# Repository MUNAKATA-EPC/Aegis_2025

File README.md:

🏆 Competition Results

<2024 Season>
Kitakyushu Node Tournament → 🥇 Champion (A Court)

Kyushu Block Tournament → 🥇 Champion, 🏅 Best Presentation Award

Japan Open 2024 Soccer Lightweight League → 31st place

<2025 Season>
Fukuoka Node Tournament → 🥇 Champion

Kyushu Block Tournament → 🥇 Champion

Japan Open 2025 Soccer Lightweight League → 🥇 Champion, 🏅 Best Presentation Award

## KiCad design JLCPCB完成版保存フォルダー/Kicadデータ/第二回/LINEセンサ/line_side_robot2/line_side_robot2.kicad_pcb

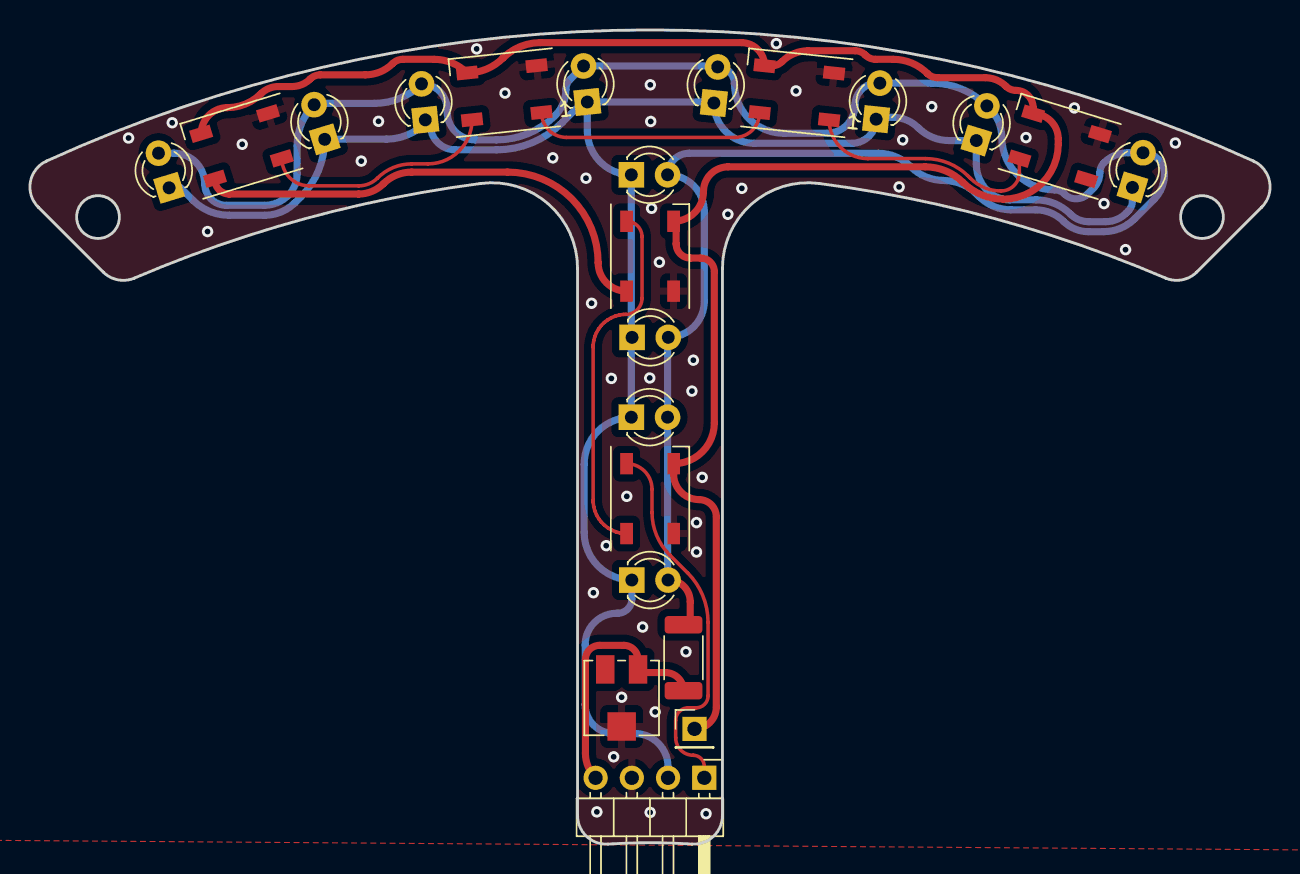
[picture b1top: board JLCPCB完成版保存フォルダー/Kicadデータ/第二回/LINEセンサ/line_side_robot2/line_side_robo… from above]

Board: 2 copper layers, 87.0 x 57.1 mm, 22 parts (0 on the bottom side), 11 nets.

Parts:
D1, D2, D3, D4, D5, D6: NeoPixel_THT; LED_WS2812B_PLCC4_5.0x5.0mm_P3.2mm
J1: Conn_01x04_Pin; PinHeader_1x04_P2.54mm_Horizontal
J2: Conn_01x01_Pin; PinHeader_1x01_P2.54mm_Vertical
Q1, Q2, Q3, Q4, Q5, Q6, Q7, Q8, Q9, Q10, Q11, Q12: Q_Photo_NPN; LED_D3.0mm_Clear
R1: 1K; R_2010_5025Metric
RV1: R_Potentiometer_Trim_US; Potentiometer_Vishay_TS53YJ_Vertical

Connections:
+3.3V: J1.2, Q1.1 (C), Q2.1 (C), Q3.1 (C), Q4.1 (C), Q5.1 (C), Q6.1 (C), Q7.1 (C), Q8.1 (C), Q9.1 (C), Q10.1 (C), Q11.1 (C), Q12.1 (C)
+5V: D1.3 (VDD), D2.3 (VDD), D3.3 (VDD), D4.3 (VDD), D5.3 (VDD), D6.3 (VDD), J2.1
/PWM: D1.4 (DIN), J1.1
/S: J1.4, R1.1, RV1.3
GND: D1.2 (GND), D2.2 (GND), D3.2 (GND), D4.2 (GND), D5.2 (GND), D6.2 (GND), J1.3, RV1.2
unnamed: D1.1 (DOUT), D2.4 (DIN)
unnamed: D2.1 (DOUT), D3.4 (DIN)
unnamed: D3.1 (DOUT), D6.4 (DIN)
unnamed: D4.4 (DIN), D6.1 (DOUT)
unnamed: D4.1 (DOUT), D5.4 (DIN)
unnamed: Q1.2 (E), Q2.2 (E), Q3.2 (E), Q4.2 (E), Q5.2 (E), Q6.2 (E), Q7.2 (E), Q8.2 (E), Q9.2 (E), Q10.2 (E), Q11.2 (E), Q12.2 (E), R1.2

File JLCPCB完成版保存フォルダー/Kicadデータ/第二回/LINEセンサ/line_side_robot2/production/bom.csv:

Designator,Footprint,Quantity,Value,LCSC Part #
"D1, D2, D3, D4, D5, D6",LED_WS2812B_PLCC4_5.0x5.0mm_P3.2mm,6,NeoPixel_THT,
J1,PinHeader_1x04_P2.54mm_Horizontal,1,Conn_01x04_Pin,
J2,PinHeader_1x01_P2.54mm_Vertical,1,Conn_01x01_Pin,
"Q1, Q10, Q11, Q12, Q2, Q3, Q4, Q5, Q6, Q7, Q8, Q9",LED_D3.0mm_Clear,12,Q_Photo_NPN,
R1,2010,1,1K,
RV1,Potentiometer_Vishay_TS53YJ_Vertical,1,R_Potentiometer_Trim_US,

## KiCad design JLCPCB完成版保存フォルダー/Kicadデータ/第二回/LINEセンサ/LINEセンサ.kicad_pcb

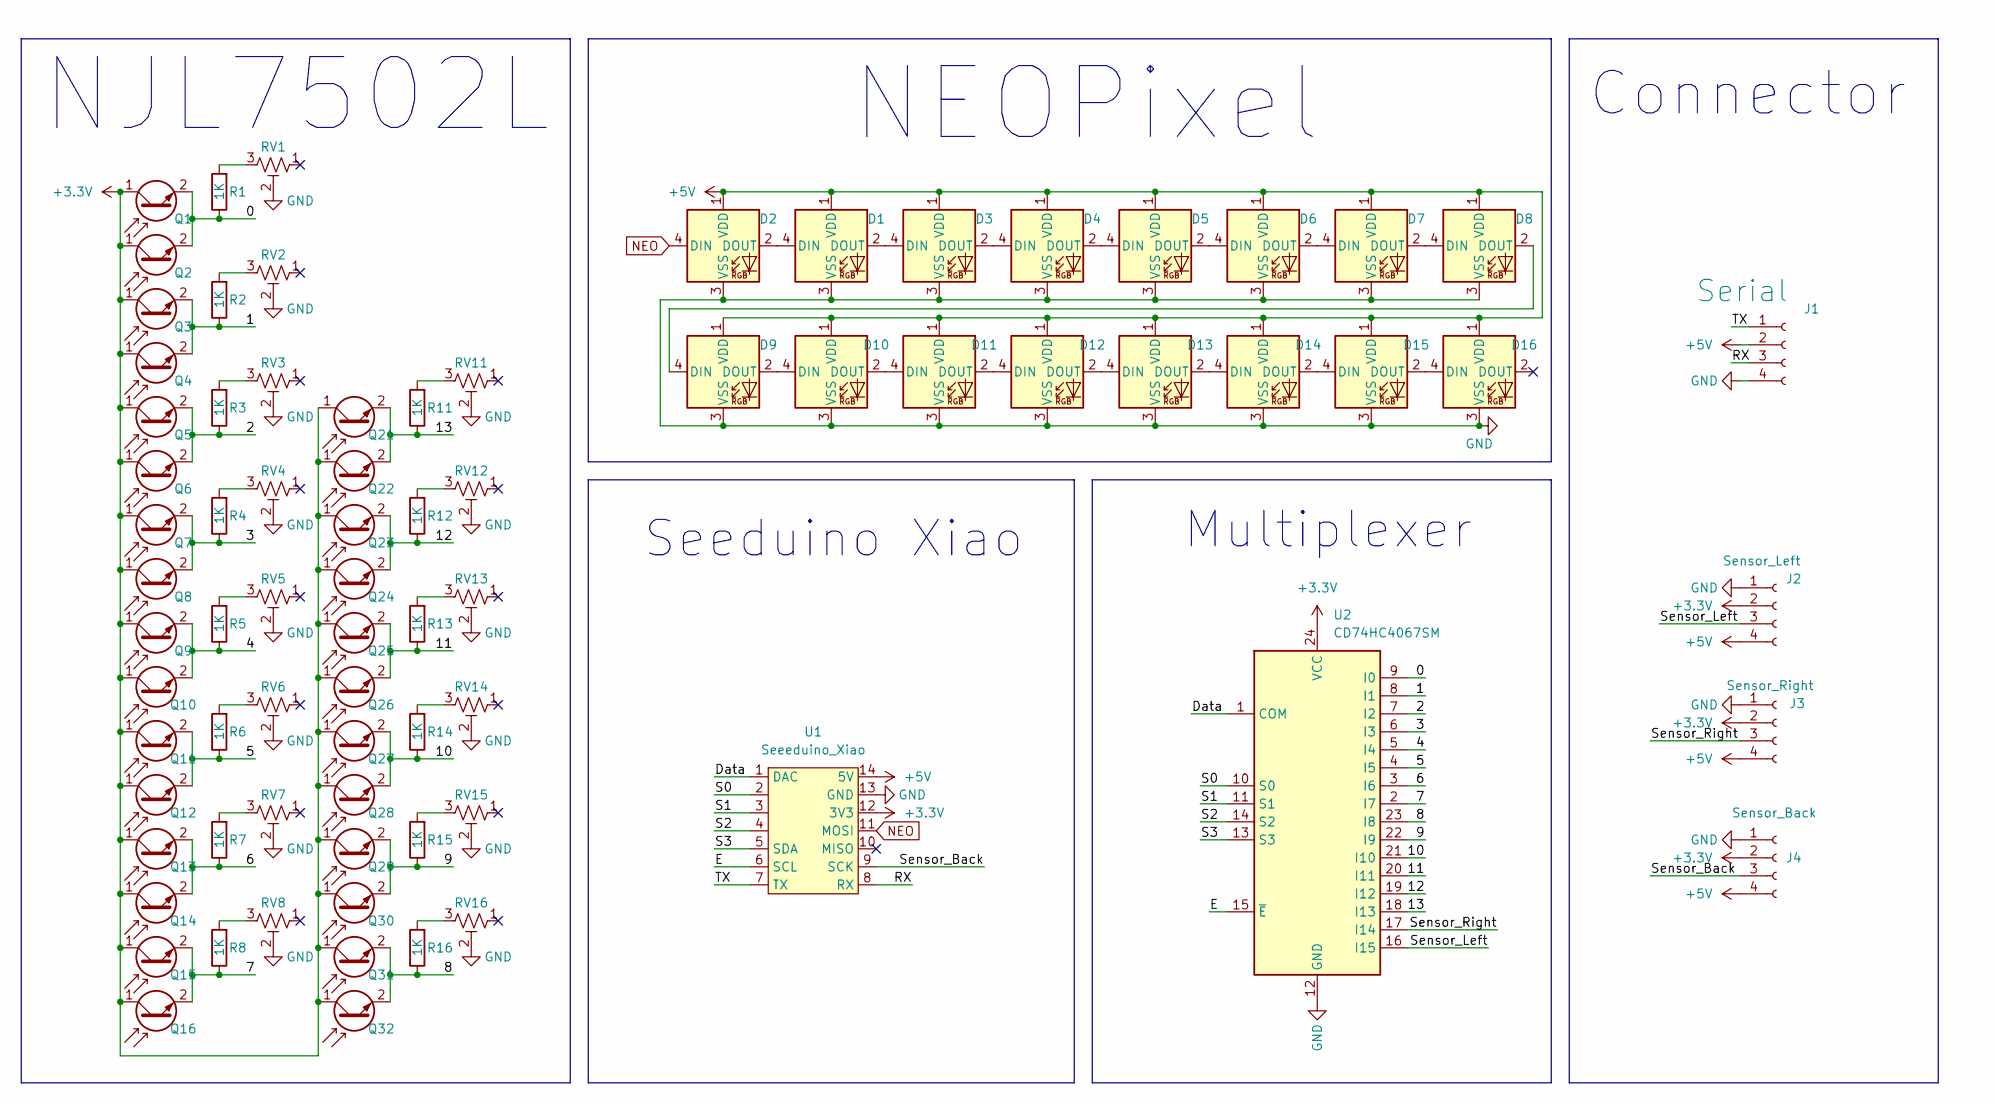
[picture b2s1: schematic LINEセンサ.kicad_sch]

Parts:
D1: WS2812B; JST_XH_B4B-XH-A_1x04_P2.50mm_Vertical
D2, D3, D4, D5, D6, D7, D8, D9, D10, D11, D12, D13, D14, D15, D16: WS2812B; LED_WS2812B-2020_PLCC4_2.0x2.0mm
J1: Serial; JST_XH_B4B-XH-A_1x04_P2.50mm_Vertical
J2: Sensor_Left; JST_XH_B4B-XH-A_1x04_P2.50mm_Vertical
J3: Sensor_Right; JST_XH_B4B-XH-A_1x04_P2.50mm_Vertical
J4: Sensor_Back; JST_XH_B4B-XH-A_1x04_P2.50mm_Vertical
Q1, Q2, Q3, Q4, Q5, Q6, Q7, Q8, Q9, Q10, Q11, Q12, Q13, Q14, Q15, Q16, Q21, Q22, Q23, Q24, Q25, Q26, Q27, Q28, Q29, Q30, Q31, Q32: Q_Photo_NPN; LED_D3.0mm_Clear
R1, R2, R3, R4, R5, R6, R7, R8, R11, R12, R13, R14, R15, R16: 1K; R_2010_5025Metric
RV1, RV2, RV3, RV4, RV5, RV6, RV7, RV8, RV11, RV12, RV13, RV14, RV15, RV16: R_Potentiometer_Trim_US; Potentiometer_Vishay_TS53YJ_Vertical
U1: Seeeduino_Xiao; seeeduinoXIAO
U2: CD74HC4067SM; SSOP-24_5.3x8.2mm_P0.65mm

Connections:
+3.3V: J2.2, J3.2, J4.2, Q1.1 (C), Q2.1 (C), Q3.1 (C), Q4.1 (C), Q5.1 (C), Q6.1 (C), Q7.1 (C), Q8.1 (C), Q9.1 (C), Q10.1 (C), Q11.1 (C), Q12.1 (C), Q13.1 (C), Q14.1 (C), Q15.1 (C), Q16.1 (C), Q21.1 (C), Q22.1 (C), Q23.1 (C), Q24.1 (C), Q25.1 (C), Q26.1 (C), Q27.1 (C), Q28.1 (C), Q29.1 (C), Q30.1 (C), Q31.1 (C), Q32.1 (C), U1.12 (3V3), U2.24 (VCC)
+5V: D1.1 (VDD), D2.1 (VDD), D3.1 (VDD), D4.1 (VDD), D5.1 (VDD), D6.1 (VDD), D7.1 (VDD), D8.1 (VDD), D9.1 (VDD), D10.1 (VDD), D11.1 (VDD), D12.1 (VDD), D13.1 (VDD), D14.1 (VDD), D15.1 (VDD), D16.1 (VDD), J1.2, J2.4, J3.4, J4.4, U1.14 (5V)
/0: Q1.2 (E), Q2.2 (E), R1.1, U2.9 (I0)
/1: Q3.2 (E), Q4.2 (E), R2.1, U2.8 (I1)
/2: Q5.2 (E), Q6.2 (E), R3.1, U2.7 (I2)
/3: Q7.2 (E), Q8.2 (E), R4.1, U2.6 (I3)
/4: Q9.2 (E), Q10.2 (E), R5.1, U2.5 (I4)
/5: Q11.2 (E), Q12.2 (E), R6.1, U2.4 (I5)
/6: Q13.2 (E), Q14.2 (E), R7.1, U2.3 (I6)
/7: Q15.2 (E), Q16.2 (E), R8.1, U2.2 (I7)
/8: Q31.2 (E), Q32.2 (E), R16.1, U2.23 (I8)
/9: Q29.2 (E), Q30.2 (E), R15.1, U2.22 (I9)
/10: Q27.2 (E), Q28.2 (E), R14.1, U2.21 (I10)
/11: Q25.2 (E), Q26.2 (E), R13.1, U2.20 (I11)
/12: Q23.2 (E), Q24.2 (E), R12.1, U2.19 (I12)
/13: Q21.2 (E), Q22.2 (E), R11.1, U2.18 (I13)
/Data: U1.1 (DAC), U2.1 (COM)
/E: U1.6 (SCL), U2.15 (~E)
/RX: J1.3, U1.8 (RX)
/S0: U1.2, U2.10 (S0)
/S1: U1.3, U2.11 (S1)
/S2: U1.4, U2.14 (S2)
/S3: U1.5 (SDA), U2.13 (S3)
/Sensor_Back: J4.3, U1.9 (SCK)
/Sensor_Left: J2.3, U2.16 (I15)
/Sensor_Right: J3.3, U2.17 (I14)
/TX: J1.1, U1.7 (TX)
GND: D1.3 (VSS), D2.3 (VSS), D3.3 (VSS), D4.3 (VSS), D5.3 (VSS), D6.3 (VSS), D7.3 (VSS), D8.3 (VSS), D9.3 (VSS), D10.3 (VSS), D11.3 (VSS), D12.3 (VSS), D13.3 (VSS), D14.3 (VSS), D15.3 (VSS), D16.3 (VSS), J1.4, J2.1, J3.1, J4.1, RV1.2, RV2.2, RV3.2, RV4.2, RV5.2, RV6.2, RV7.2, RV8.2, RV11.2, RV12.2, RV13.2, RV14.2, RV15.2, RV16.2, U1.13 (GND), U2.12 (GND)
NEO: D2.4 (DIN), U1.11 (MOSI)
unnamed: D1.4 (DIN), D2.2 (DOUT)
unnamed: D1.2 (DOUT), D3.4 (DIN)
unnamed: D3.2 (DOUT), D4.4 (DIN)
unnamed: D4.2 (DOUT), D5.4 (DIN)
unnamed: D5.2 (DOUT), D6.4 (DIN)
unnamed: D6.2 (DOUT), D7.4 (DIN)
unnamed: D7.2 (DOUT), D8.4 (DIN)
unnamed: D8.2 (DOUT), D9.4 (DIN)
unnamed: D9.2 (DOUT), D10.4 (DIN)
unnamed: D10.2 (DOUT), D11.4 (DIN)
unnamed: D11.2 (DOUT), D12.4 (DIN)
unnamed: D12.2 (DOUT), D13.4 (DIN)
unnamed: D13.2 (DOUT), D14.4 (DIN)
unnamed: D14.2 (DOUT), D15.4 (DIN)
unnamed: D15.2 (DOUT), D16.4 (DIN)
unnamed: R1.2, RV1.3
unnamed: R2.2, RV2.3
unnamed: R3.2, RV3.3
unnamed: R4.2, RV4.3
unnamed: R5.2, RV5.3
unnamed: R6.2, RV6.3
unnamed: R7.2, RV7.3
unnamed: R8.2, RV8.3
unnamed: R11.2, RV11.3
unnamed: R12.2, RV12.3
unnamed: R13.2, RV13.3
unnamed: R14.2, RV14.3
unnamed: R15.2, RV15.3
unnamed: R16.2, RV16.3

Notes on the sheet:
NJL7502L
Seeduino Xiao
NEOPixel
Multiplexer
Connector

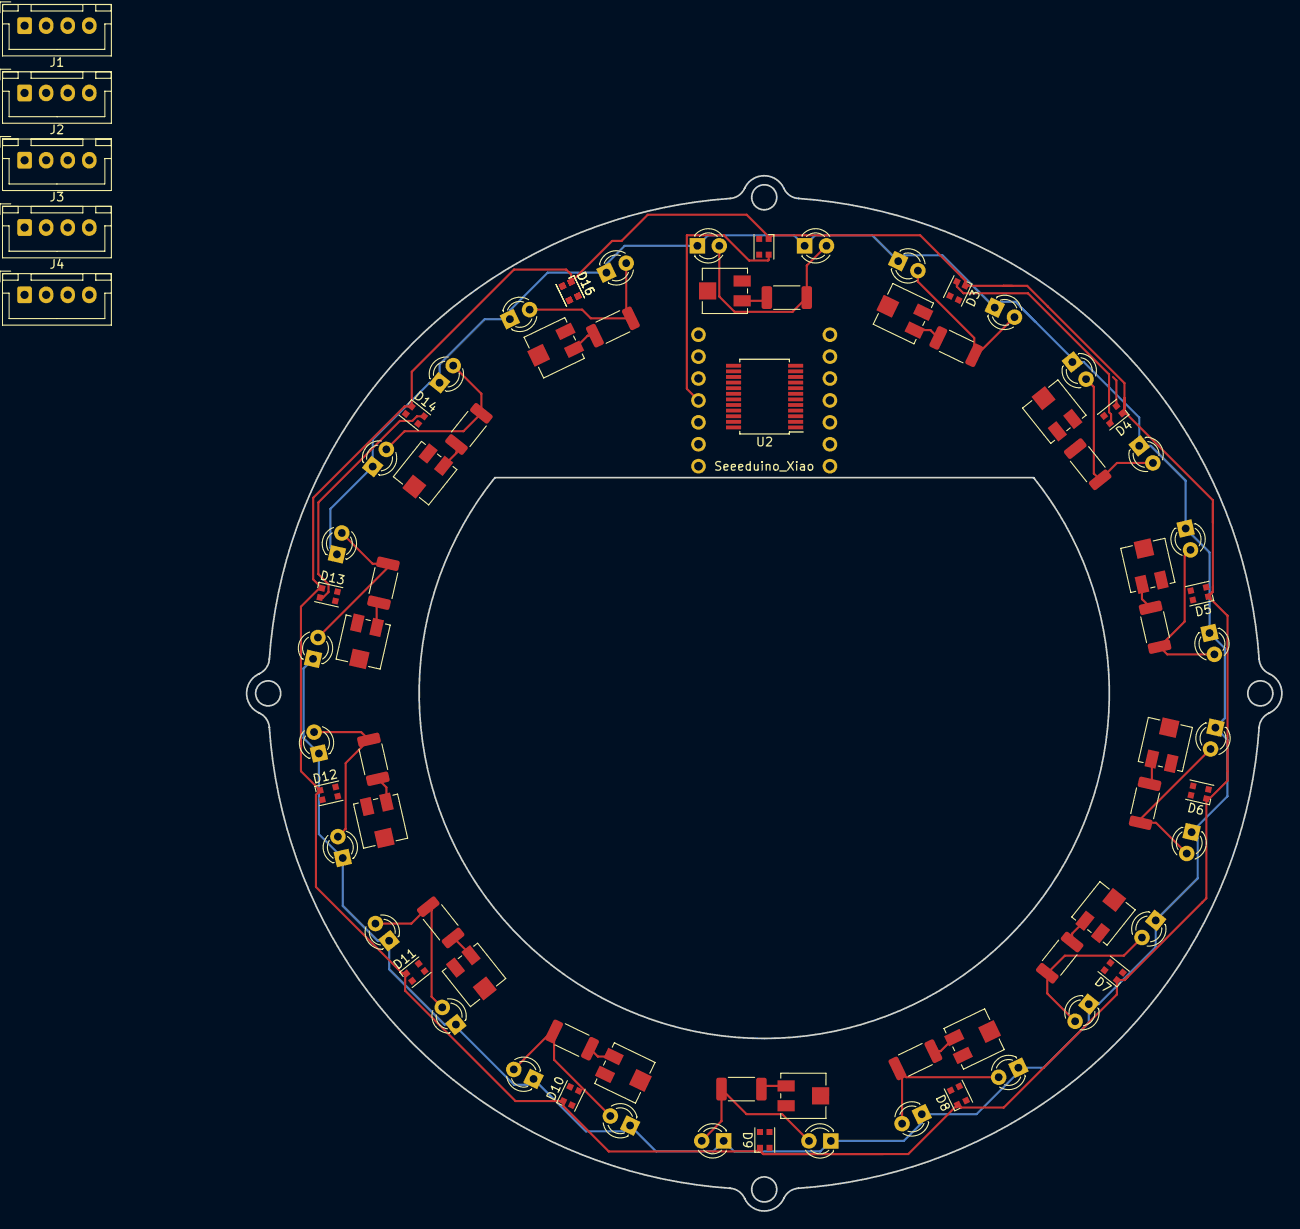
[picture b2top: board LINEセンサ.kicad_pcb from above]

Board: 2 copper layers, 120.0 x 120.0 mm, 78 parts (0 on the bottom side), 58 nets.

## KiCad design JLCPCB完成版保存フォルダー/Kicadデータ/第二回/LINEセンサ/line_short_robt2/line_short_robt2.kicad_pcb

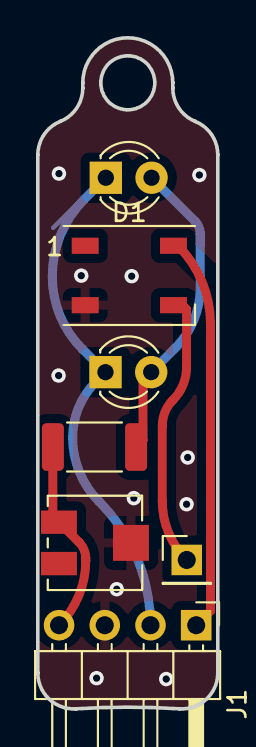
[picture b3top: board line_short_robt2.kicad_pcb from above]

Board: 2 copper layers, 10.0 x 37.3 mm, 7 parts (0 on the bottom side), 6 nets.

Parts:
D1: NeoPixel_THT; LED_WS2812B_PLCC4_5.0x5.0mm_P3.2mm
J1: Conn_01x04_Pin; PinHeader_1x04_P2.54mm_Horizontal
J2: Conn_01x01_Pin; PinHeader_1x01_P2.54mm_Vertical
Q1, Q2: Q_Photo_NPN; LED_D3.0mm_Clear
R1: 1K; R_2010_5025Metric
RV1: R_Potentiometer_Trim_US; Potentiometer_Vishay_TS53YJ_Vertical

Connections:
+3.3V: J1.2, Q1.1 (C), Q2.1 (C)
+5V: D1.3 (VDD), J2.1
/PWM: D1.4 (DIN), J1.1
/S: J1.4, R1.1, RV1.3
GND: D1.2 (GND), J1.3, RV1.2
unnamed: Q1.2 (E), Q2.2 (E), R1.2

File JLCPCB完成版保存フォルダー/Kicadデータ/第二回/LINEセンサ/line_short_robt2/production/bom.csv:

Designator,Footprint,Quantity,Value,LCSC Part #
D1,LED_WS2812B_PLCC4_5.0x5.0mm_P3.2mm,1,NeoPixel_THT,
J1,PinHeader_1x04_P2.54mm_Horizontal,1,Conn_01x04_Pin,
J2,PinHeader_1x01_P2.54mm_Vertical,1,Conn_01x01_Pin,
"Q1, Q2",LED_D3.0mm_Clear,2,Q_Photo_NPN,
R1,2010,1,1K,
RV1,Potentiometer_Vishay_TS53YJ_Vertical,1,R_Potentiometer_Trim_US,

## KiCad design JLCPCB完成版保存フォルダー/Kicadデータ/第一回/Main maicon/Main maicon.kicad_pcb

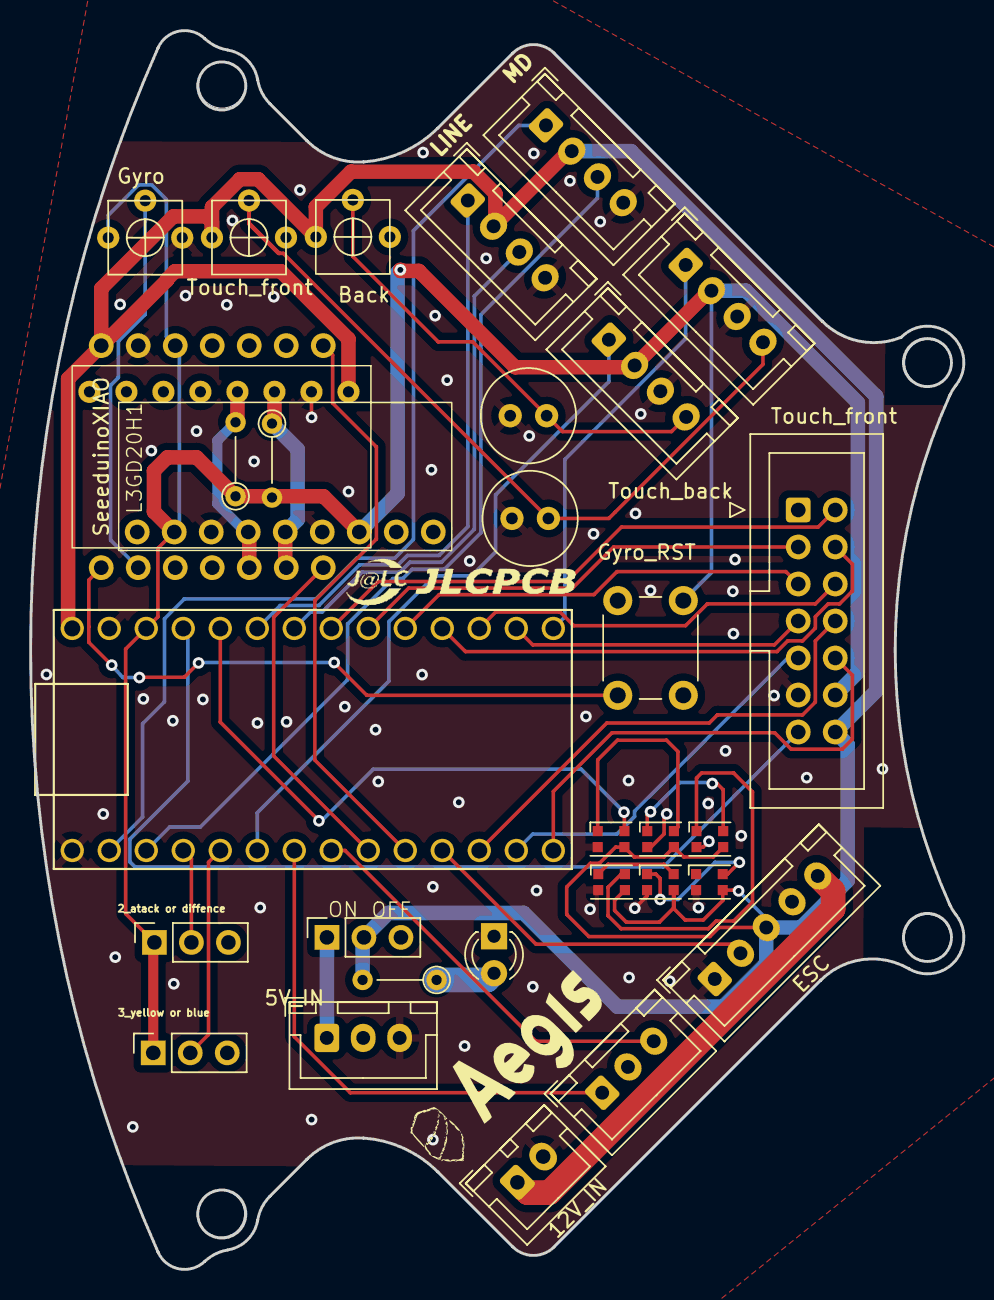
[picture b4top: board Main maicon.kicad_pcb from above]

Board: 2 copper layers, 64.1 x 85.0 mm, 32 parts (0 on the bottom side), 41 nets.

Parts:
BNO1: BNO00
Back: R_Potentiometer_Trim_US; Variable_Register
C1, C2: C; C_Radial_D6.3mm_H5.0mm_P2.50mm
D1: LED; LED_D3.0mm_Clear
D2, D3, D4, D5, D6, D7: NeoPixel_THT; LED_WS2812B-2020_PLCC4_2.0x2.0mm
J1: 12V_IN; JST_XH_B2B-XH-A_1x02_P2.50mm_Vertical
J2, J3: MD; JST_XH_B4B-XH-A_1x04_P2.50mm_Vertical
J4, J9: Conn_01x04_Pin; JST_XH_B4B-XH-A_1x04_P2.50mm_Vertical
J5, J7: Conn_01x03_Pin; JST_XH_B3B-XH-A_1x03_P2.50mm_Vertical
J6: Conn_01x05_Pin; JST_XH_B5B-XH-A_1x05_P2.50mm_Vertical
J8: Conn_02x07_Top_Bottom; IDC-Header_2x07_P2.54mm_Vertical
L3GD20H1: L3GD20OH
R1, R2, R3: R; R_Axial_DIN0204_L3.6mm_D1.6mm_P5.08mm_Vertical
RV1, RV2: R_Potentiometer_Trim_US; Variable_Register
SW1, SW2, SW3: SW_DPST_x2; PinSocket_1x03_P2.54mm_Vertical
SW4: SW_Push; SW_PUSH_6mm_H5mm
U1: Teensy4.0; Teensy40
U2: SeeeduinoXIAO; seeeduinoXIAO

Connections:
5V_IN: J5.1, SW1.1 (A)
+3.3V: J4.2, J8.12, J9.2, L3GD20H1.2 (VIN), L3GD20H1.7 (CS), R2.1, R3.2, RV2.1, SW2.1 (A), SW3.1 (A), SW4.1, U1.31 (3V3), U2.12 (3V3)
+5V: BNO1.1 (VIN), Back.1, D2.3 (VDD), D3.3 (VDD), D4.3 (VDD), D5.3 (VDD), D6.3 (VDD), D7.3 (VDD), J2.2, J3.2, J6.3, J8.14, R1.2, RV1.1, SW1.2 (B), U1.33 (VIN), U2.14 (5V)
+12V: J1.1, J6.5
CN1_Touch_sensor: J4.1, U1.20 (13_SCK_CRX1_LED)
CN2_Touch_sensor: J9.1, U1.6 (4_BCLK2)
ESC: J6.2, U1.11 (9_OUT1C)
FET1: J7.1, U1.7 (5_IN2)
FET2: J7.3, U1.8 (6_OUT1D)
GND: BNO1.2 (GND), C1.1, C2.1, D1.1 (K), D2.2 (GND), D3.2 (GND), D4.2 (GND), D5.2 (GND), D6.2 (GND), D7.2 (GND), J1.2, J2.4, J3.4, J4.3, J5.3, J6.1, J6.4, J7.2, J8.11, J9.3, L3GD20H1.3 (GND), L3GD20H1.6 (SDO/SAO), RV2.3, U1.1 (GND), U1.32 (GND), U2.13 (GND)
Gyairo_RST_Switch: SW4.2, U2.1 (PA02_A0_D0)
LCD-TeensyD10: J8.8, U1.12 (10_CS_MQSR)
LCD-TeensyD11: J8.9, U1.13 (11_MOSI_CTX1)
LCD-TeensyD12: J8.10, U1.14 (12_MISO_MQSL)
LED1: C1.2, J4.4, RV1.2
LED2: Back.2, C2.2, J9.4
NEO: D2.4 (DIN), U1.29 (22_A8_CTX1)
unnamed: D1.2 (A), R1.1
unnamed: D2.1 (DOUT), D3.4 (DIN)
unnamed: D3.1 (DOUT), D4.4 (DIN)
unnamed: D4.1 (DOUT), D5.4 (DIN)
unnamed: D5.1 (DOUT), D6.4 (DIN)
unnamed: D6.1 (DOUT), D7.4 (DIN)
RV: RV2.2, U2.2 (PA4_A1_D1)
RX_Boll: J8.5, U1.24 (17_A3_TX4_SDA1)
RX_Gyairo: U1.10 (8_TX2_IN1), U2.8 (PB09_A7_D7_RX)
RX_Line: J3.3, U1.27 (20_A6_TX5_LRCLK1)
RX_MD: J2.3, U1.3 (1_TX1_CTX2_MISO1)
RX_camera: J8.7, U1.21 (14_A0_TX3_SPDIF_OUT)
SCL: BNO1.3 (SCL), L3GD20H1.5 (SCL/SPC), R3.1, U2.6 (PA9_A5_D5_SCL)
SCL_LCD: J8.2, U1.26 (19_A5_SCL0)
SDA: BNO1.4 (SDA), L3GD20H1.4 (SDA/SDI/SDO), R2.2, U2.5 (PA8_A4_D4_SDA)
SDA_LCD: J8.3, U1.25 (18_A4_SDA0)
TX_Boll: J8.4, U1.23 (16_A2_RX4_SCL1)
TX_Gyairo: U1.9 (7_RX2_OUT1A), U2.7 (PB08_A6_D6_TX)
TX_Line: J3.1, U1.28 (21_A7_RX5_BCLK1)
TX_MD: J2.1, U1.2 (0_RX1_CRX2_CS1)
TX_camera: J8.6, U1.22 (15_A1_RX3_SPDIF_IN)
Tougle_Switch_atack or diffence: SW2.2 (B), U1.4 (2_OUT2)
Tougle_switch_ yellow or blue: SW3.2 (B), U1.5 (3_LRCLK2)
switch: J8.13, U1.30 (23_A9_CRX1_MCLK1)

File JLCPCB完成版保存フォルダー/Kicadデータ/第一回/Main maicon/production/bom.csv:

Designator,Footprint,Quantity,Value,LCSC Part #
"BACK, RV1, RV2",Variable_Register,3,R_Potentiometer_Trim_US,
BNO1,BNO00,1,~,
"C1, C2",C_Radial_D6.3mm_H5.0mm_P2.50mm,2,C,
D1,LED_D3.0mm_Clear,1,LED,
"D2, D3, D4, D5, D6, D7",LED_WS2812B-2020_PLCC4_2.0x2.0mm,6,NeoPixel_THT,
J1,JST_XH_B2B-XH-A_1x02_P2.50mm_Vertical,1,12V_IN,
"J2, J3",JST_XH_B4B-XH-A_1x04_P2.50mm_Vertical,2,MD,
"J4, J9",JST_XH_B4B-XH-A_1x04_P2.50mm_Vertical,2,Conn_01x04_Pin,
"J5, J7",JST_XH_B3B-XH-A_1x03_P2.50mm_Vertical,2,Conn_01x03_Pin,
J6,JST_XH_B5B-XH-A_1x05_P2.50mm_Vertical,1,Conn_01x05_Pin,
J8,IDC-Header_2x07_P2.54mm_Vertical,1,Conn_02x07_Top_Bottom,
L3GD20H1,L3GD20OH,1,~,
"R1, R2, R3",R_Axial_DIN0204_L3.6mm_D1.6mm_P5.08mm_Vertical,3,R,
"SW1, SW2, SW3",PinSocket_1x03_P2.54mm_Vertical,3,SW_DPST_x2,
SW4,SW_PUSH_6mm_H5mm,1,SW_Push,
U1,Teensy40,1,Teensy4.0,
U2,seeeduinoXIAO,1,SeeeduinoXIAO,

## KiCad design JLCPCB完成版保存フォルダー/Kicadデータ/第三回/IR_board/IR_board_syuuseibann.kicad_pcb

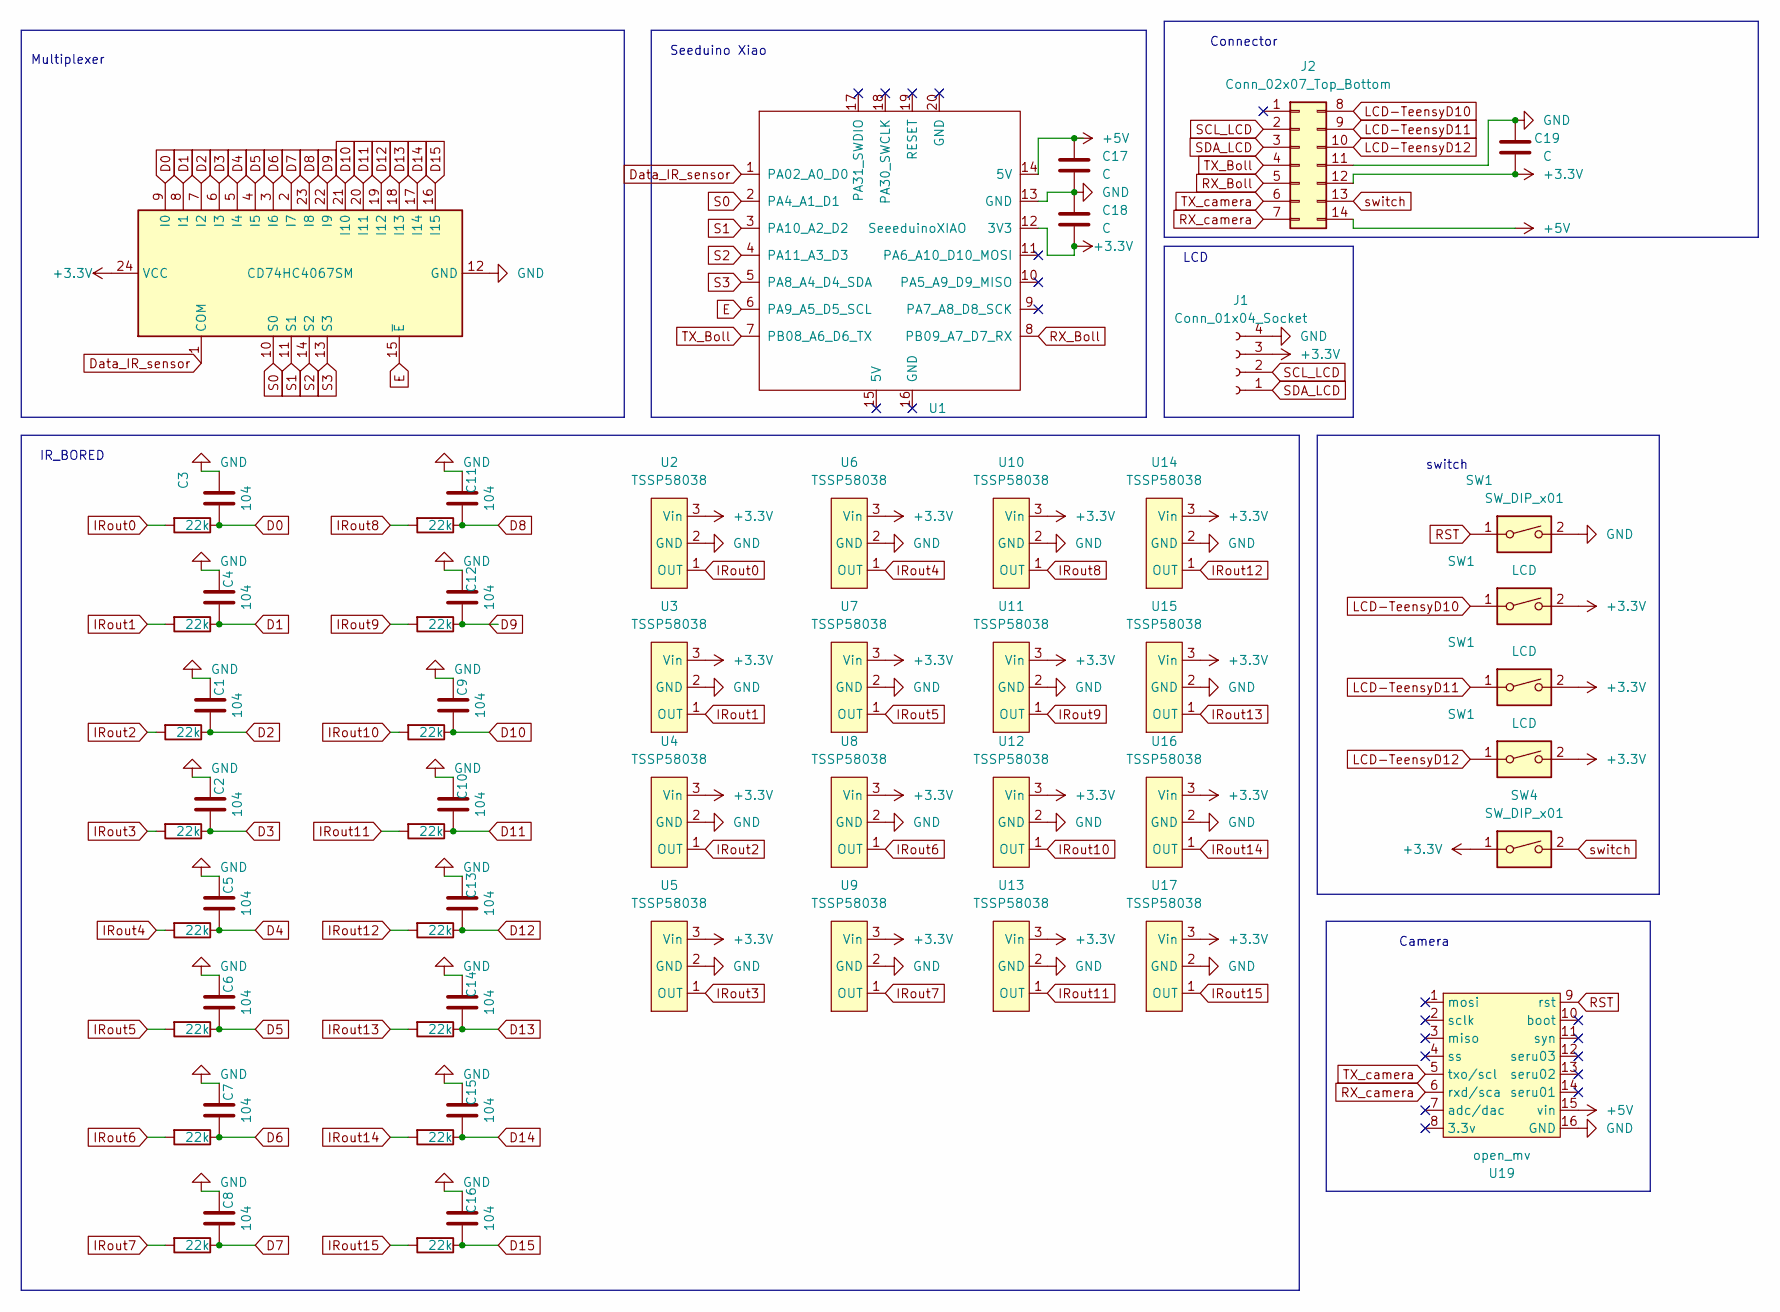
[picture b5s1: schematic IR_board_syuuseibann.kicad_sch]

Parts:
C1, C2, C3, C4, C5, C6, C7, C8, C9, C10, C11, C12, C13, C14, C15, C16: 104; C_Disc_D5.0mm_W2.5mm_P2.50mm
C17, C18, C19: C; C_Disc_D5.0mm_W2.5mm_P2.50mm
J1: Conn_01x04_Socket; PinHeader_1x04_P2.54mm_Vertical
J2: Conn_02x07_Top_Bottom; IDC-Header_2x07_P2.54mm_Vertical
R1, R2, R3, R4, R5, R6, R7, R8, R9, R10, R11, R12, R13, R14, R15, R16: 22k; R_Axial_DIN0204_L3.6mm_D1.6mm_P5.08mm_Vertical
SW1: LCD; SW_PUSH_6mm_H5mm
SW4: SW_DIP_x01; PinHeader_1x02_P2.54mm_Vertical
U1: SeeeduinoXIAO; seeeduinoXIAO
U2, U3, U4, U5, U6, U7, U8, U9, U10, U11, U12, U13, U14, U15, U16, U17: TSSP58038; PinHeader_1x03_P2.54mm_Vertical
U18: CD74HC4067SM; SSOP-24_5.3x8.2mm_P0.65mm
U19: open_mv; OpenMV

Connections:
+3.3V: C18.2, C19.2, J1.3, J2.12, SW1.2, SW4.1, U1.12 (3V3), U2.3 (Vin), U3.3 (Vin), U4.3 (Vin), U5.3 (Vin), U6.3 (Vin), U7.3 (Vin), U8.3 (Vin), U9.3 (Vin), U10.3 (Vin), U11.3 (Vin), U12.3 (Vin), U13.3 (Vin), U14.3 (Vin), U15.3 (Vin), U16.3 (Vin), U17.3 (Vin), U18.24 (VCC); also elsewhere on the board
+5V: C17.1, J2.14, U1.14 (5V), U19.15 (vin)
D0: C3.1, R3.1, U18.9 (I0)
D1: C4.1, R4.1, U18.8 (I1)
D2: C1.1, R1.1, U18.7 (I2)
D3: C2.1, R2.1, U18.6 (I3)
D4: C5.1, R5.1, U18.5 (I4)
D5: C6.1, R6.1, U18.4 (I5)
D6: C7.1, R7.1, U18.3 (I6)
D7: C8.1, R8.1, U18.2 (I7)
D8: C11.1, R11.1, U18.23 (I8)
D9: C12.1, R12.1, U18.22 (I9)
D10: C9.1, R9.1, U18.21 (I10)
D11: C10.1, R10.1, U18.20 (I11)
D12: C13.1, R13.1, U18.19 (I12)
D13: C14.1, R14.1, U18.18 (I13)
D14: C15.1, R15.1, U18.17 (I14)
D15: C16.1, R16.1, U18.16 (I15)
Data_IR_sensor: U1.1 (PA02_A0_D0), U18.1 (COM)
E: U1.6 (PA9_A5_D5_SCL), U18.15 (~E)
GND: C1.2, C2.2, C3.2, C4.2, C5.2, C6.2, C7.2, C8.2, C9.2, C10.2, C11.2, C12.2, C13.2, C14.2, C15.2, C16.2, C17.2, C18.1, C19.1, J1.4, J2.11, SW1.2, U1.13 (GND), U2.2 (GND), U3.2 (GND), U4.2 (GND), U5.2 (GND), U6.2 (GND), U7.2 (GND), U8.2 (GND), U9.2 (GND), U10.2 (GND), U11.2 (GND), U12.2 (GND), U13.2 (GND), U14.2 (GND), U15.2 (GND), U16.2 (GND), U17.2 (GND), U18.12 (GND), U19.16 (GND); also elsewhere on the board
IRout0: R3.2, U2.1 (OUT)
IRout1: R4.2, U3.1 (OUT)
IRout2: R1.2, U4.1 (OUT)
IRout3: R2.2, U5.1 (OUT)
IRout4: R5.2, U6.1 (OUT)
IRout5: R6.2, U7.1 (OUT)
IRout6: R7.2, U8.1 (OUT)
IRout7: R8.2, U9.1 (OUT)
IRout8: R11.2, U10.1 (OUT)
IRout9: R12.2, U11.1 (OUT)
IRout10: R9.2, U12.1 (OUT)
IRout11: R10.2, U13.1 (OUT)
IRout12: R13.2, U14.1 (OUT)
IRout13: R14.2, U15.1 (OUT)
IRout14: R15.2, U16.1 (OUT)
IRout15: R16.2, U17.1 (OUT)
LCD-TeensyD10: J2.8, SW1.1; also elsewhere on the board
LCD-TeensyD11: J2.9; also elsewhere on the board
LCD-TeensyD12: J2.10, SW1.1; also elsewhere on the board
RST: SW1.1, U19.9 (rst); also elsewhere on the board
RX_Boll: J2.5, U1.8 (PB09_A7_D7_RX)
RX_camera: J2.7, U19.6 (rxd/sca)
S0: U1.2 (PA4_A1_D1), U18.10 (S0)
S1: U1.3 (PA10_A2_D2), U18.11 (S1)
S2: U1.4 (PA11_A3_D3), U18.14 (S2)
S3: U1.5 (PA8_A4_D4_SDA), U18.13 (S3)
SCL_LCD: J1.2, J2.2
SDA_LCD: J1.1, J2.3
TX_Boll: J2.4, U1.7 (PB08_A6_D6_TX)
TX_camera: J2.6, U19.5 (txo/scl)
switch: J2.13, SW4.2

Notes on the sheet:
LCD
switch
Multiplexer
Camera
IR_BORED
Connector
Seeduino Xiao

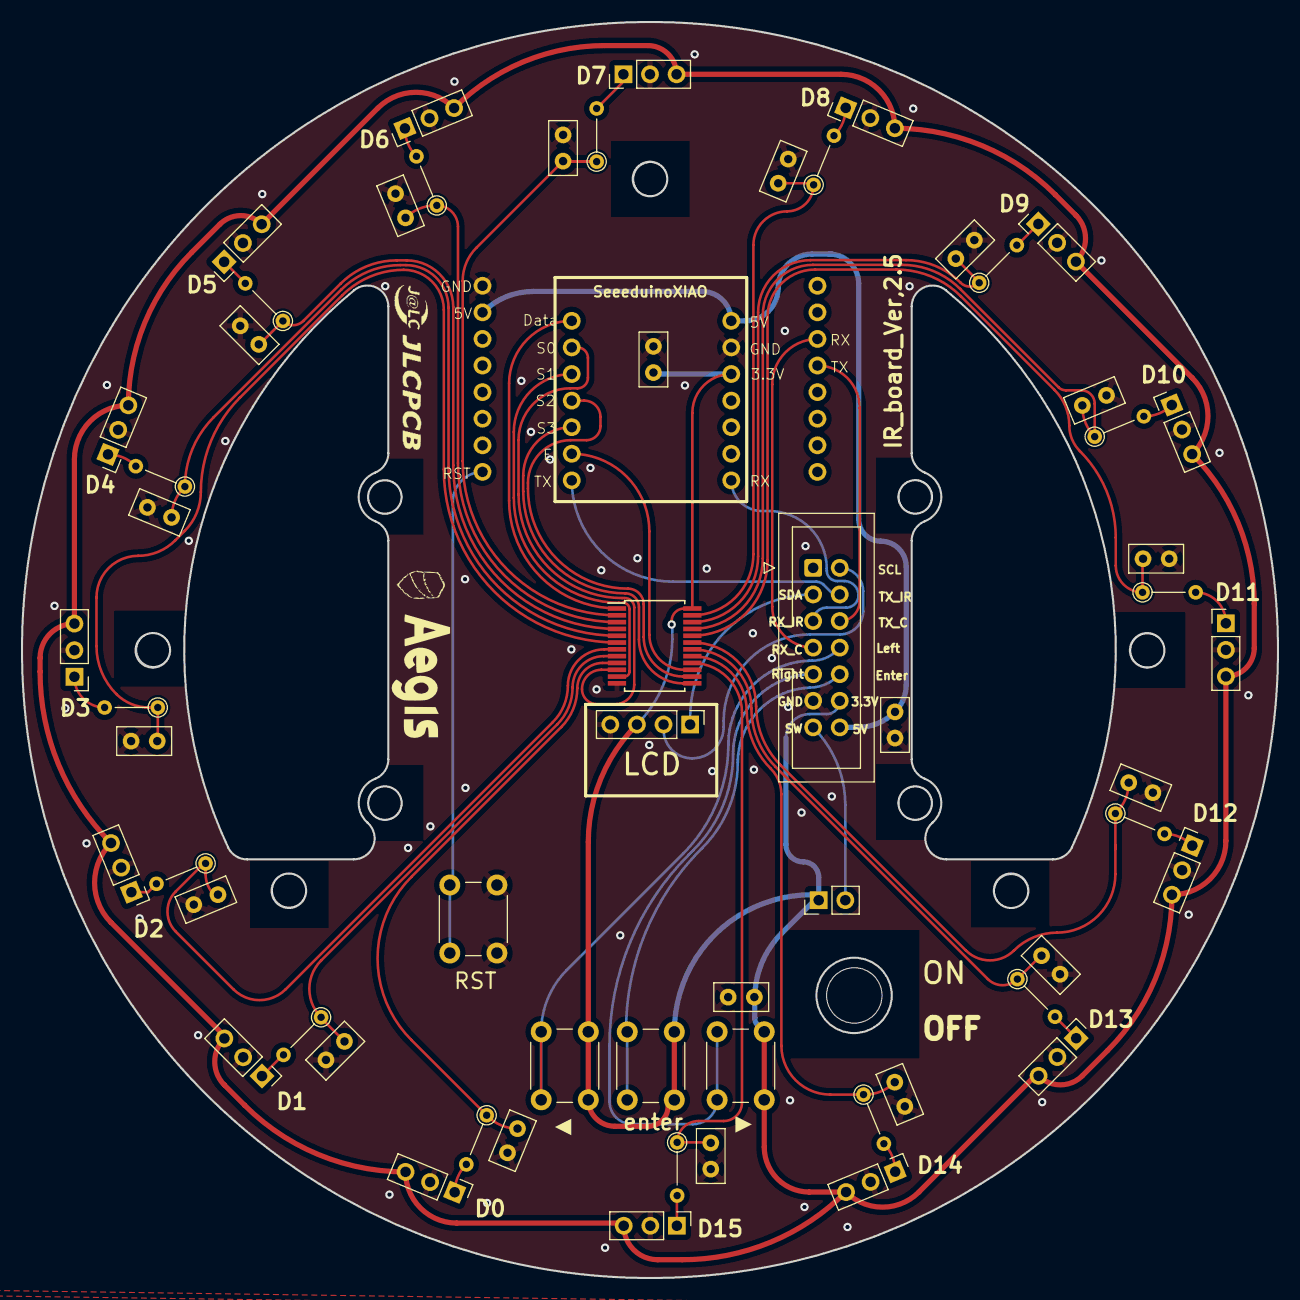
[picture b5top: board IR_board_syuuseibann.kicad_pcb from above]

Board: 2 copper layers, 120.0 x 120.0 mm, 61 parts (0 on the bottom side), 52 nets.

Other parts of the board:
RST: SW_DIP_x01; SW_PUSH_6mm_H5mm
SW3: LCD; SW_PUSH_6mm_H5mm
enter: LCD; SW_PUSH_6mm_H5mm
▶: LCD; SW_PUSH_6mm_H5mm

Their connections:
+3.3V: SW3.2, enter.2, ▶.2; also elsewhere on the board
GND: RST.2; also elsewhere on the board
LCD-TeensyD10: ▶.1; also elsewhere on the board
LCD-TeensyD11: SW3.1; also elsewhere on the board
LCD-TeensyD12: enter.1; also elsewhere on the board
RST: RST.1; also elsewhere on the board

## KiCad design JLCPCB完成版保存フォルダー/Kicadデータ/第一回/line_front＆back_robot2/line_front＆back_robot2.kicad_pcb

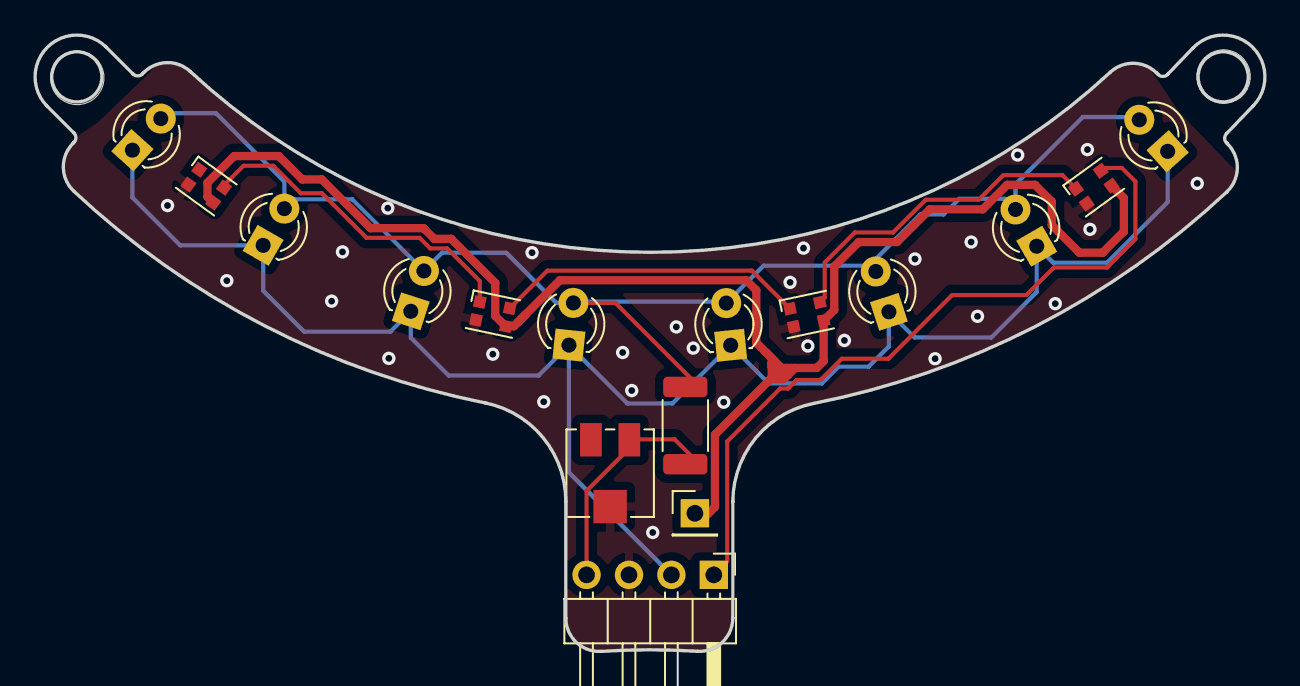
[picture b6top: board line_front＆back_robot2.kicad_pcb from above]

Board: 2 copper layers, 73.6 x 36.9 mm, 16 parts (0 on the bottom side), 9 nets.

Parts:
D1, D2, D3, D5: NeoPixel_THT; LED_WS2812B-2020_PLCC4_2.0x2.0mm
J2: Conn_01x04_Pin; PinHeader_1x04_P2.54mm_Horizontal
J3: Conn_01x01_Pin; PinHeader_1x01_P2.54mm_Vertical
Q1, Q2, Q3, Q4, Q7, Q8, Q9, Q10: Q_Photo_NPN; LED_D3.0mm_Clear
R8: 1K; R_2010_5025Metric
RV2: R_Potentiometer_Trim_US; Potentiometer_Vishay_TS53YJ_Vertical

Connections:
+3.3V: J2.2, Q1.1 (C), Q2.1 (C), Q3.1 (C), Q4.1 (C), Q7.1 (C), Q8.1 (C), Q9.1 (C), Q10.1 (C)
+5V: D1.3 (VDD), D2.3 (VDD), D3.3 (VDD), D5.3 (VDD), J3.1
/PWM: D3.4 (DIN), J2.1
/S: J2.4, R8.1, RV2.3
GND: D1.2 (GND), D2.2 (GND), D3.2 (GND), D5.2 (GND), J2.3, RV2.2
unnamed: D1.4 (DIN), D5.1 (DOUT)
unnamed: D2.4 (DIN), D3.1 (DOUT)
unnamed: D2.1 (DOUT), D5.4 (DIN)
unnamed: Q1.2 (E), Q2.2 (E), Q3.2 (E), Q4.2 (E), Q7.2 (E), Q8.2 (E), Q9.2 (E), Q10.2 (E), R8.2

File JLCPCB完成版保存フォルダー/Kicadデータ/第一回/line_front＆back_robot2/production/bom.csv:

Designator,Footprint,Quantity,Value,LCSC Part #
"D1, D2, D3, D5",LED_WS2812B-2020_PLCC4_2.0x2.0mm,4,NeoPixel_THT,
J2,PinHeader_1x04_P2.54mm_Horizontal,1,Conn_01x04_Pin,
J3,PinHeader_1x01_P2.54mm_Vertical,1,Conn_01x01_Pin,
"Q1, Q10, Q2, Q3, Q4, Q7, Q8, Q9",LED_D3.0mm_Clear,8,Q_Photo_NPN,
R8,2010,1,1K,
RV2,Potentiometer_Vishay_TS53YJ_Vertical,1,R_Potentiometer_Trim_US,

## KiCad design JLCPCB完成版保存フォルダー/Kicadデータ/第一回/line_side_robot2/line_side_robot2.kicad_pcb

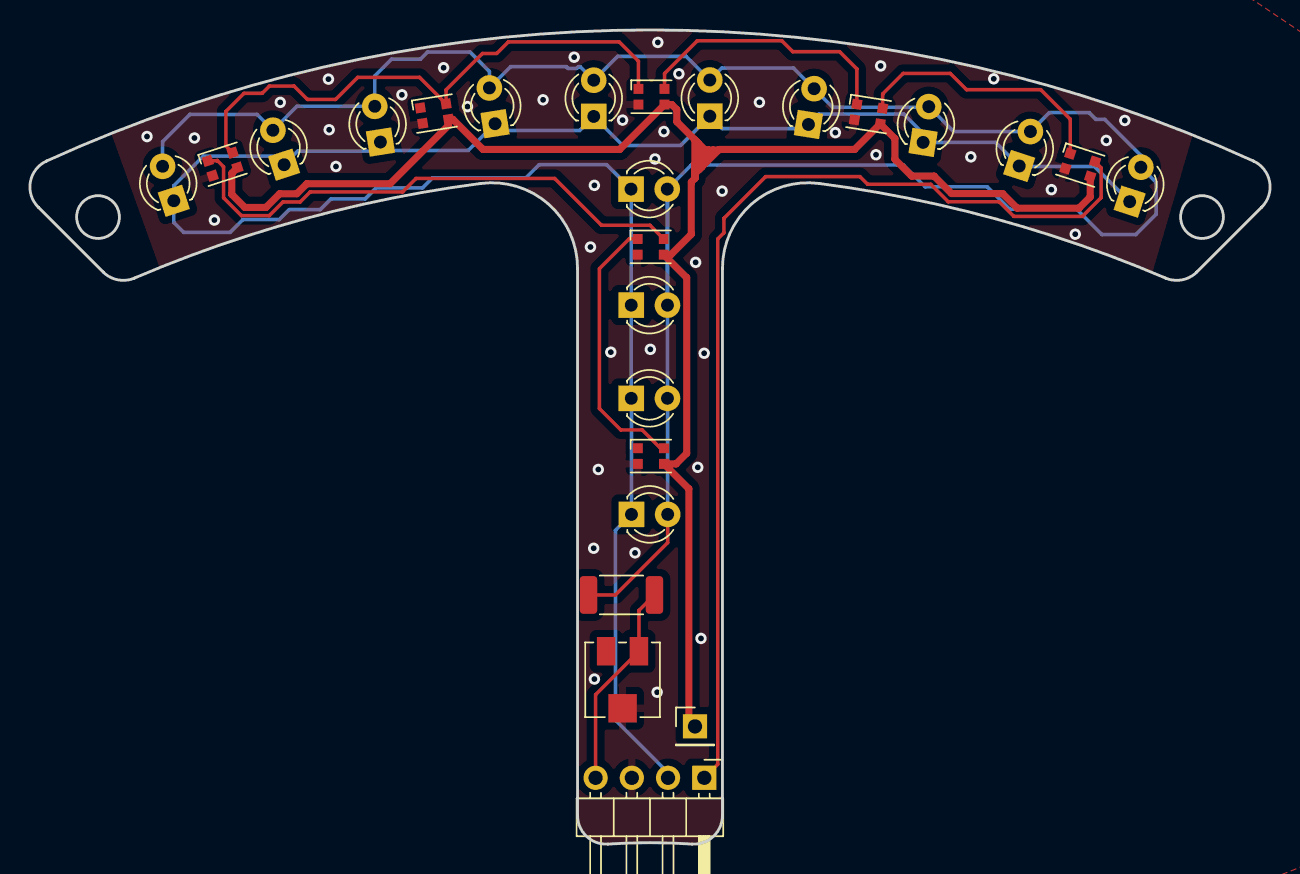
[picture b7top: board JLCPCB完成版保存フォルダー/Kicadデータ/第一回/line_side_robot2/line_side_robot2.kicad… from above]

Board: 2 copper layers, 87.0 x 57.1 mm, 25 parts (0 on the bottom side), 11 nets.

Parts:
D1, D2, D3, D4, D4#2, D5, D6: NeoPixel_THT; LED_WS2812B-2020_PLCC4_2.0x2.0mm
J1: Conn_01x04_Pin; PinHeader_1x04_P2.54mm_Horizontal
J2: Conn_01x01_Pin; PinHeader_1x01_P2.54mm_Vertical
Q1, Q2, Q3, Q4, Q5, Q6, Q7, Q8, Q9, Q10, Q11, Q12, Q13, Q14: Q_Photo_NPN; LED_D3.0mm_Clear
R1: 1K; R_2010_5025Metric
RV1: R_Potentiometer_Trim_US; Potentiometer_Vishay_TS53YJ_Vertical

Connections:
+3.3V: J1.2, Q1.1 (C), Q2.1 (C), Q3.1 (C), Q4.1 (C), Q5.1 (C), Q6.1 (C), Q7.1 (C), Q8.1 (C), Q9.1 (C), Q10.1 (C), Q11.1 (C), Q12.1 (C), Q13.1 (C), Q14.1 (C)
+5V: D1.3 (VDD), D2.3 (VDD), D3.3 (VDD), D4.3 (VDD), D4#2.3 (VDD), D5.3 (VDD), D6.3 (VDD), J2.1
/PWM: D1.4 (DIN), J1.1
/S: J1.4, R1.1, RV1.3
GND: D1.2 (GND), D2.2 (GND), D3.2 (GND), D4.2 (GND), D4#2.2 (GND), D5.2 (GND), D6.2 (GND), J1.3, RV1.2
unnamed: D1.1 (DOUT), D2.4 (DIN)
unnamed: D2.1 (DOUT), D3.4 (DIN)
unnamed: D3.1 (DOUT), D4.4 (DIN), D6.4 (DIN)
unnamed: D4#2.4 (DIN), D6.1 (DOUT)
unnamed: D4#2.1 (DOUT), D5.4 (DIN)
unnamed: Q1.2 (E), Q2.2 (E), Q3.2 (E), Q4.2 (E), Q5.2 (E), Q6.2 (E), Q7.2 (E), Q8.2 (E), Q9.2 (E), Q10.2 (E), Q11.2 (E), Q12.2 (E), Q13.2 (E), Q14.2 (E), R1.2

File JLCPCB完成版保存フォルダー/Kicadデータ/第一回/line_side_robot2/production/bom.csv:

Designator,Footprint,Quantity,Value,LCSC Part #
"D1, D2, D3, D4_2, D4, D5, D6",LED_WS2812B-2020_PLCC4_2.0x2.0mm,7,NeoPixel_THT,
J1,PinHeader_1x04_P2.54mm_Horizontal,1,Conn_01x04_Pin,
J2,PinHeader_1x01_P2.54mm_Vertical,1,Conn_01x01_Pin,
"Q1, Q10, Q11, Q12, Q13, Q14, Q2, Q3, Q4, Q5, Q6, Q7, Q8, Q9",LED_D3.0mm_Clear,14,Q_Photo_NPN,
R1,2010,1,1K,
RV1,Potentiometer_Vishay_TS53YJ_Vertical,1,R_Potentiometer_Trim_US,
